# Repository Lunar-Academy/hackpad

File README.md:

Small arrow key macropad to use with a 60% keyboard

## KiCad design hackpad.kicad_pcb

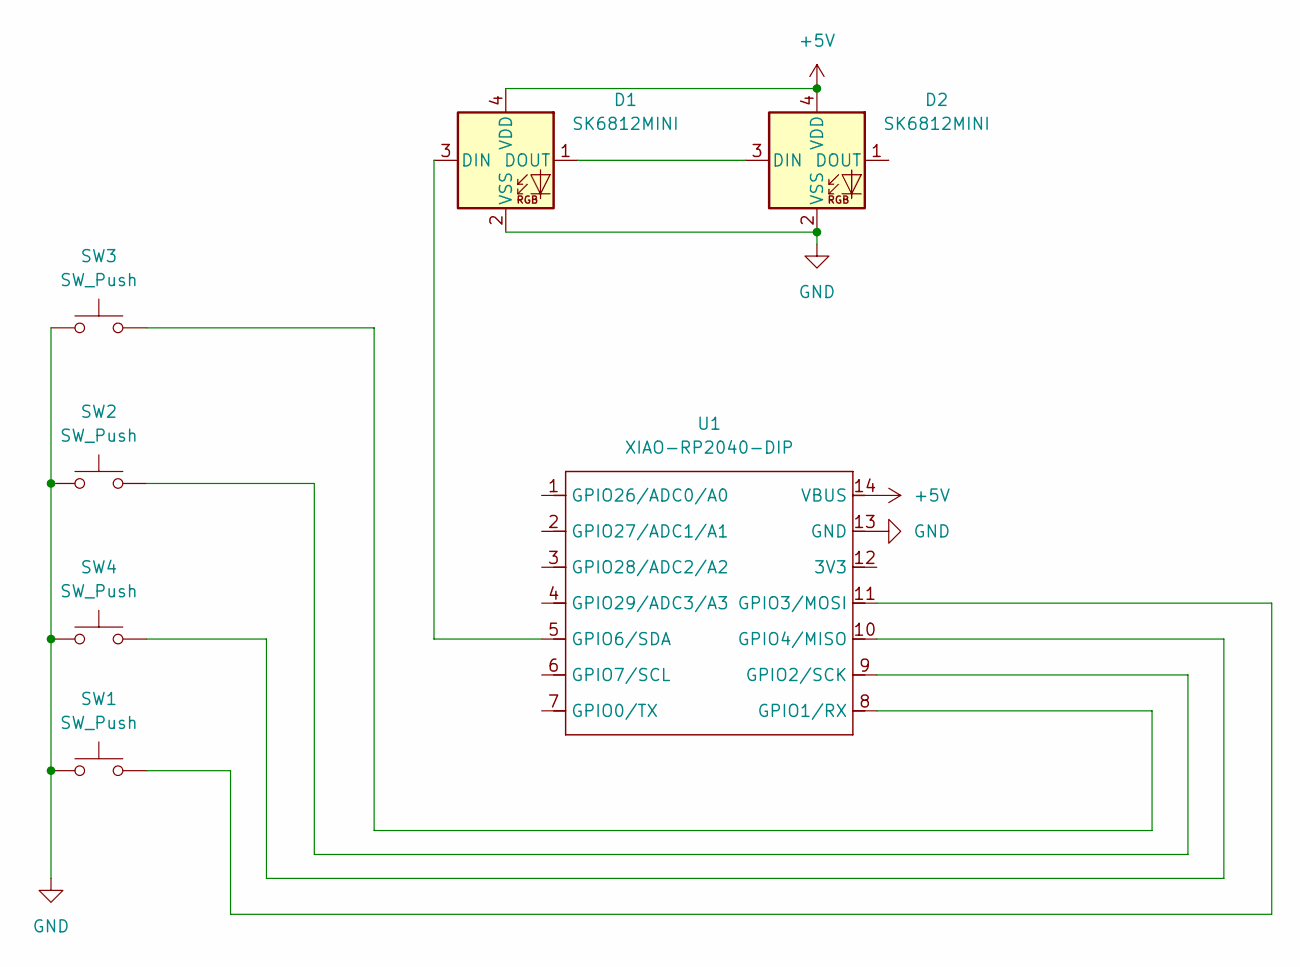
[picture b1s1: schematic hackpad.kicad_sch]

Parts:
D1, D2: SK6812MINI; LED_SK6812MINI_PLCC4_3.5x3.5mm_P1.75mm
SW1, SW2, SW3, SW4: SW_Push; SW_Cherry_MX_1.00u_PCB
U1: XIAO-RP2040-DIP

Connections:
+5V: D1.4 (VDD), D2.4 (VDD), U1.14 (VBUS)
GND: D1.2 (VSS), D2.2 (VSS), SW1.1, SW2.1, SW3.1, SW4.1, U1.13 (GND)
unnamed: D1.3 (DIN), U1.5 (GPIO6/SDA)
unnamed: D1.1 (DOUT), D2.3 (DIN)
unnamed: SW3.2, U1.8 (GPIO1/RX)
unnamed: SW2.2, U1.9 (GPIO2/SCK)
unnamed: SW1.2, U1.11 (GPIO3/MOSI)
unnamed: SW4.2, U1.10 (GPIO4/MISO)

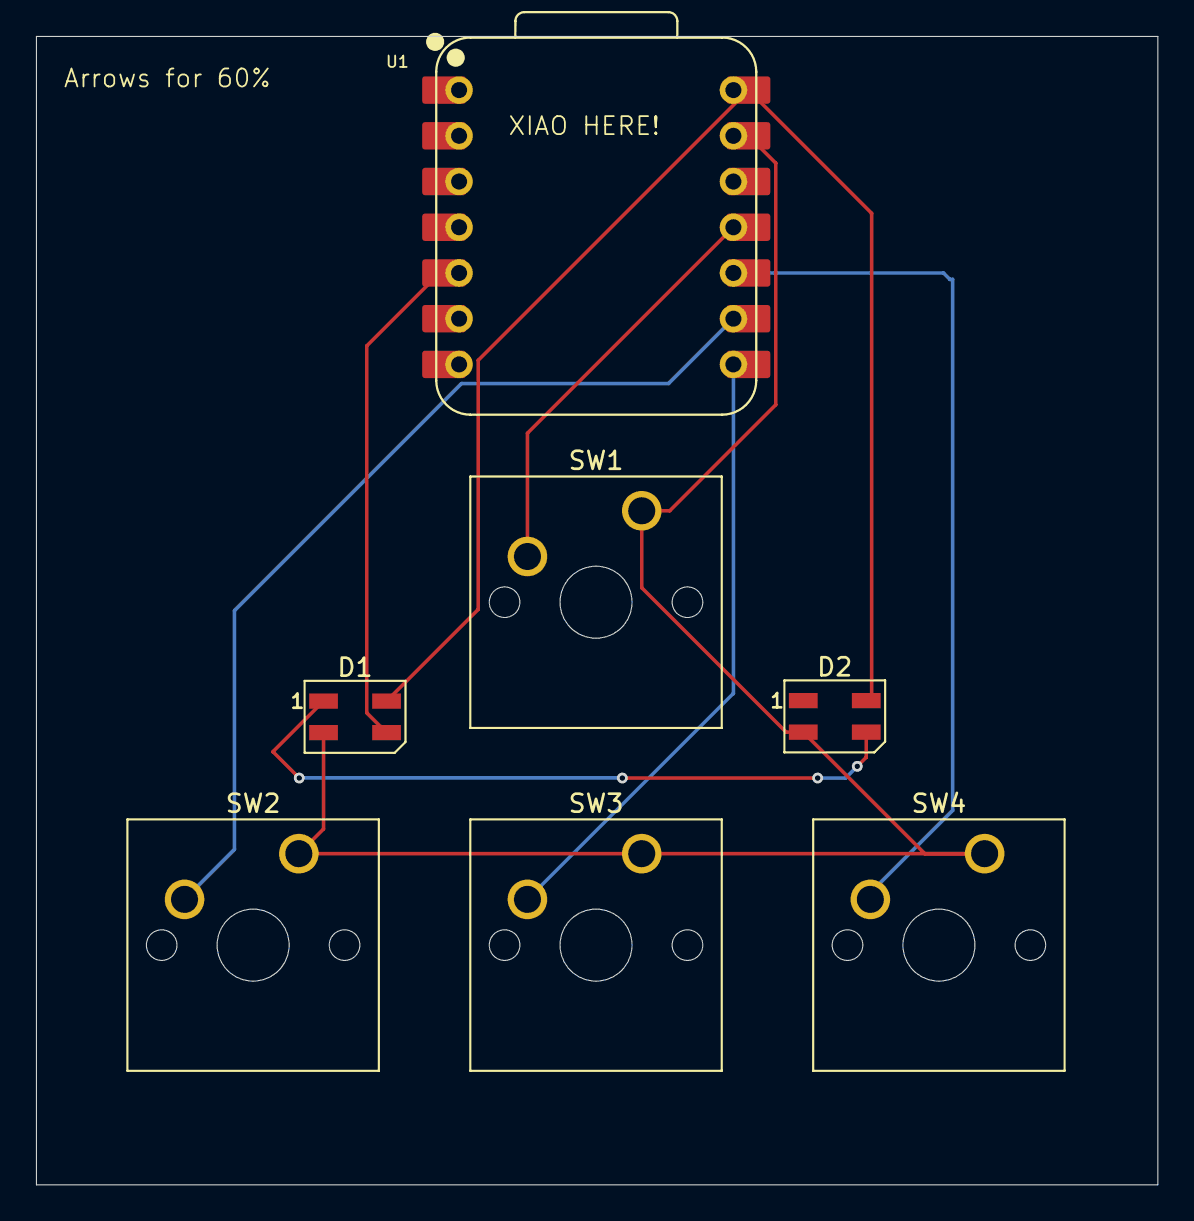
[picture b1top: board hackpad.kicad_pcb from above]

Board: 2 copper layers, 62.3 x 63.8 mm, 7 parts (0 on the bottom side), 8 nets.

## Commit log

2025-09-06 Add README with project description and image
